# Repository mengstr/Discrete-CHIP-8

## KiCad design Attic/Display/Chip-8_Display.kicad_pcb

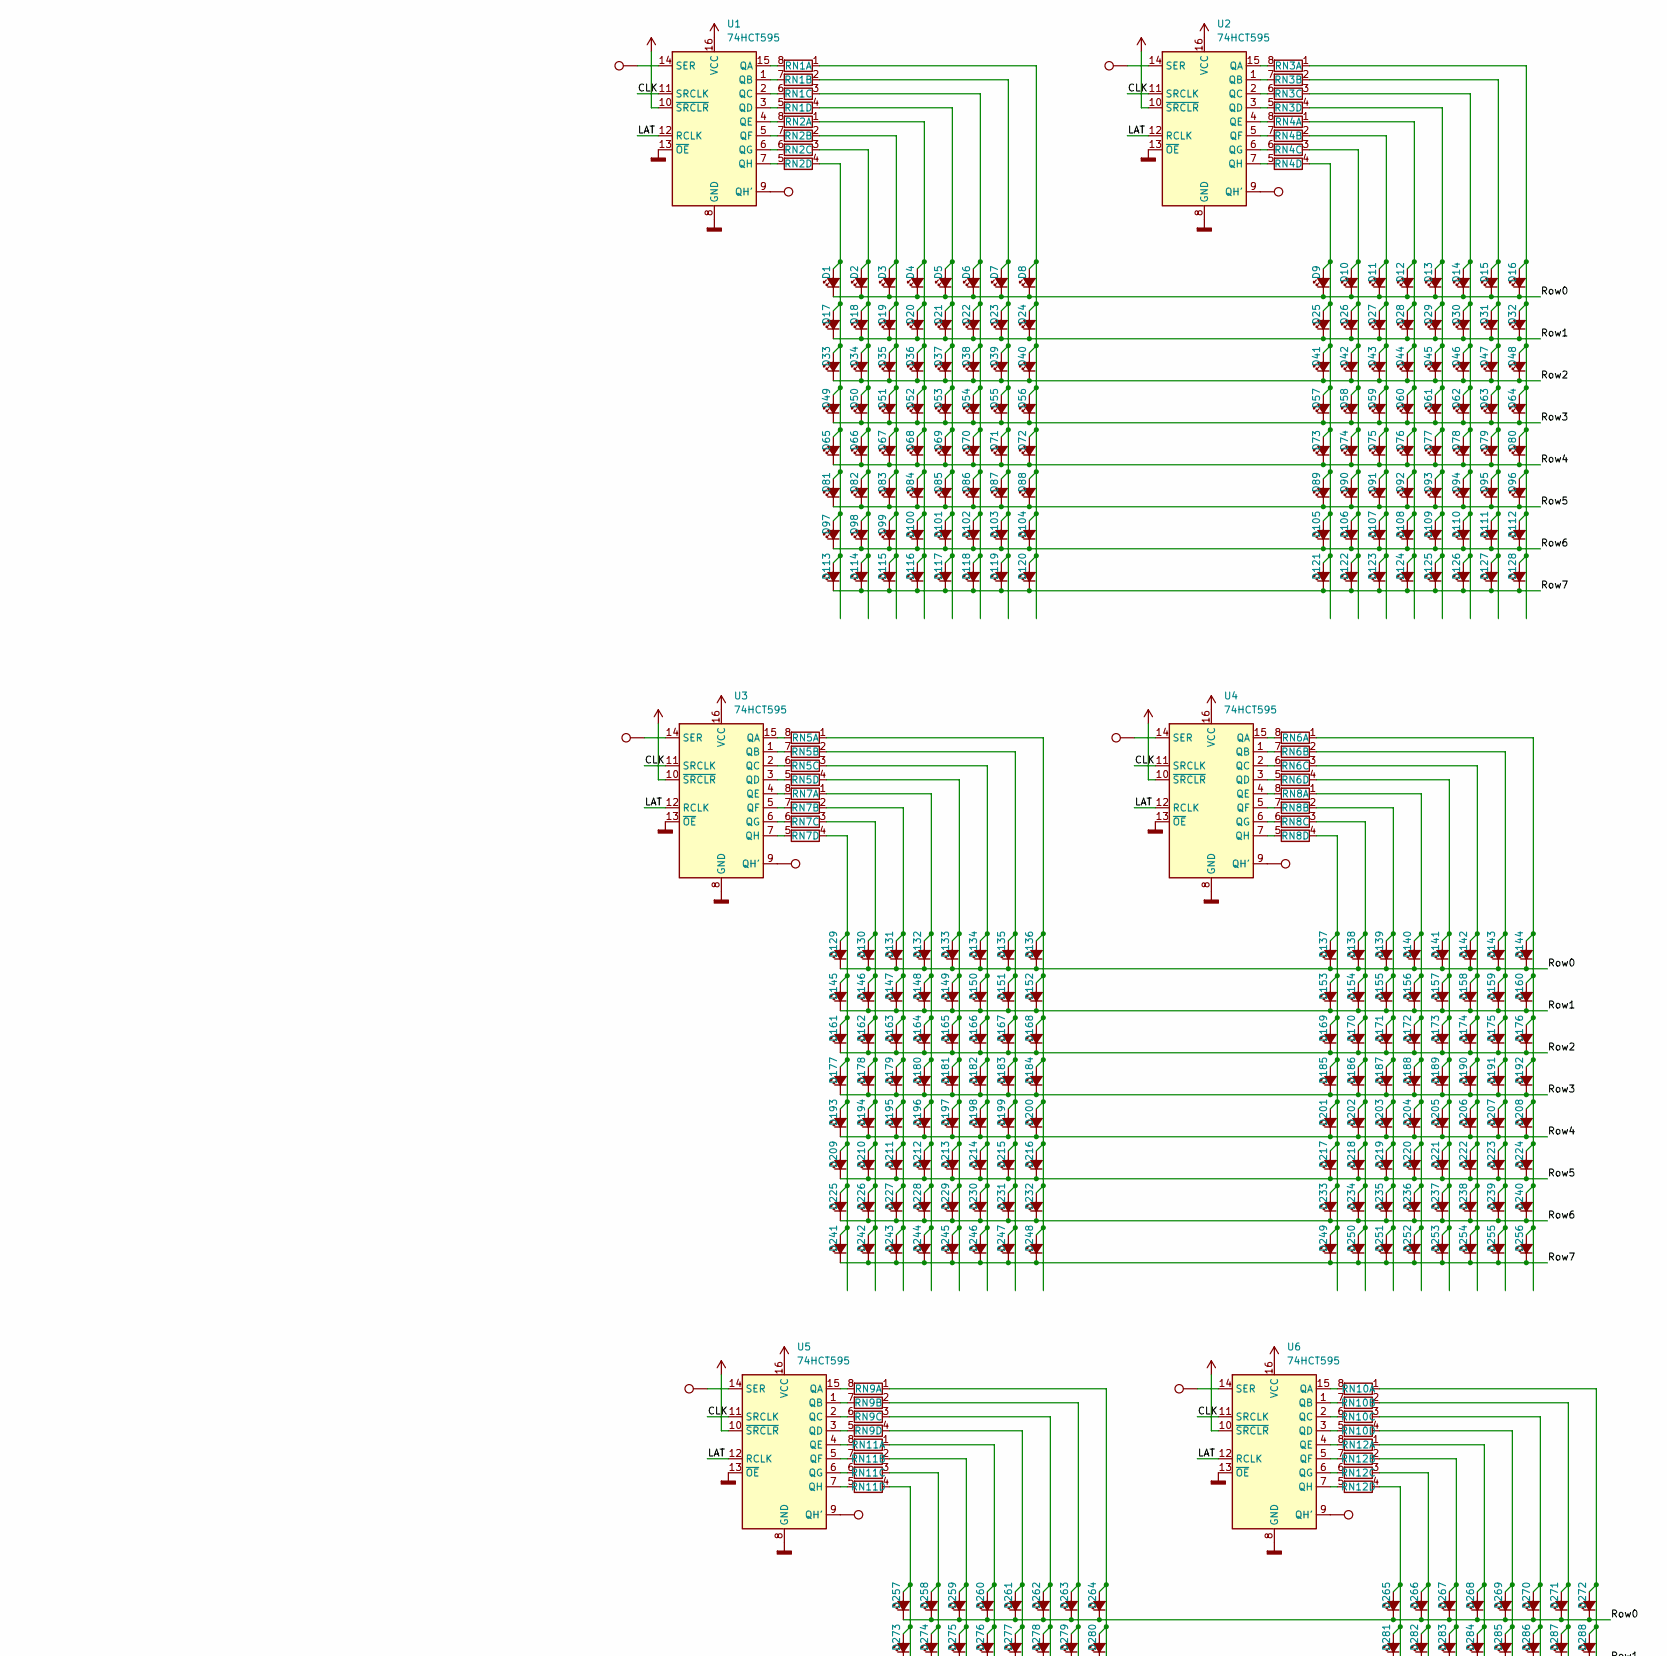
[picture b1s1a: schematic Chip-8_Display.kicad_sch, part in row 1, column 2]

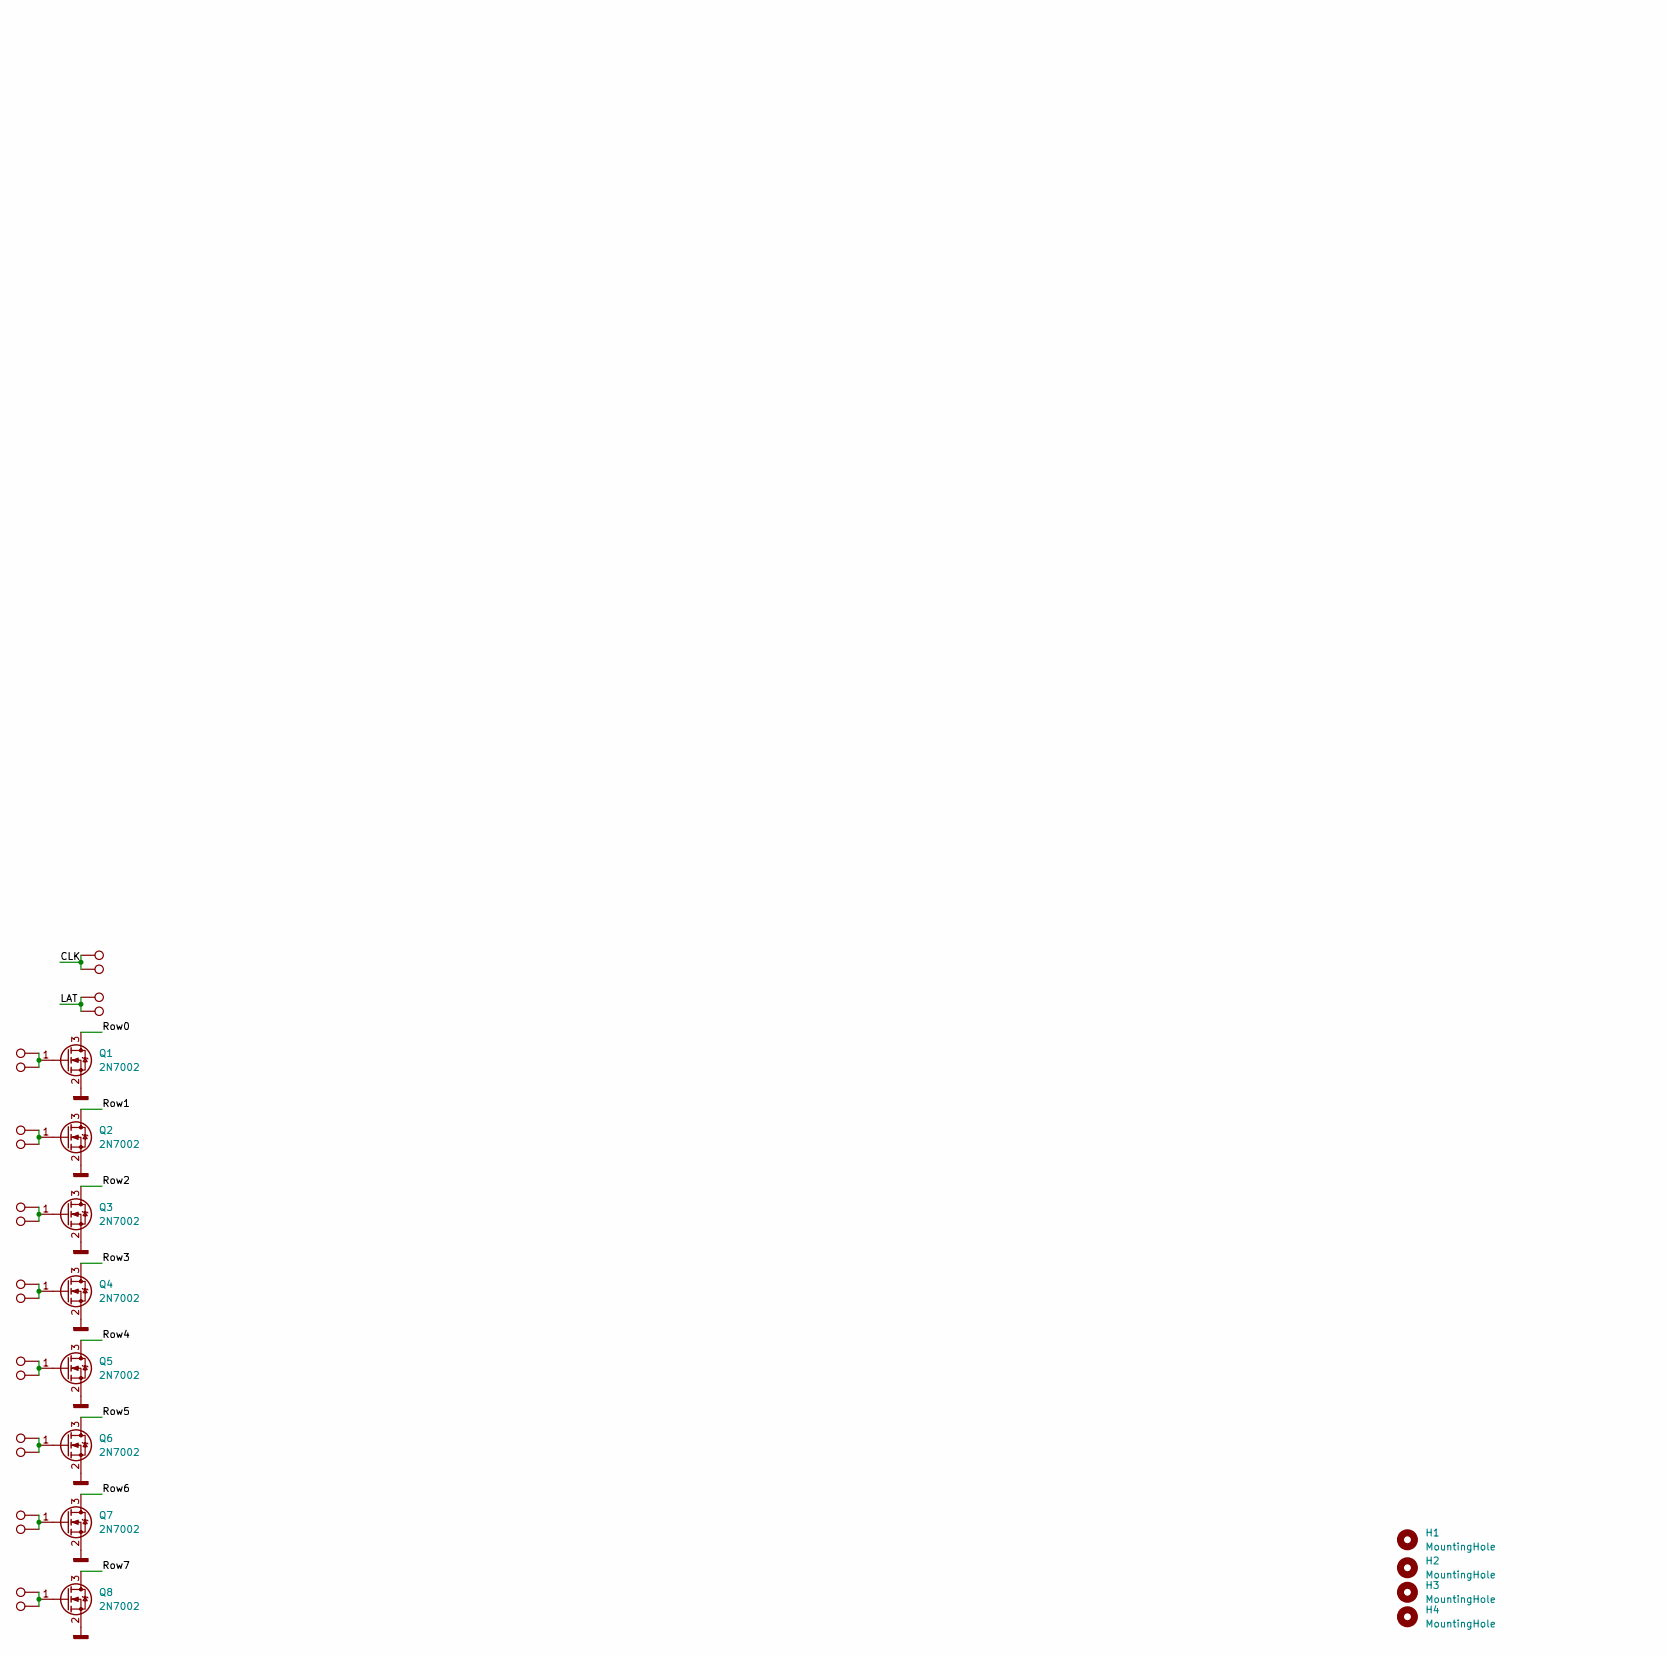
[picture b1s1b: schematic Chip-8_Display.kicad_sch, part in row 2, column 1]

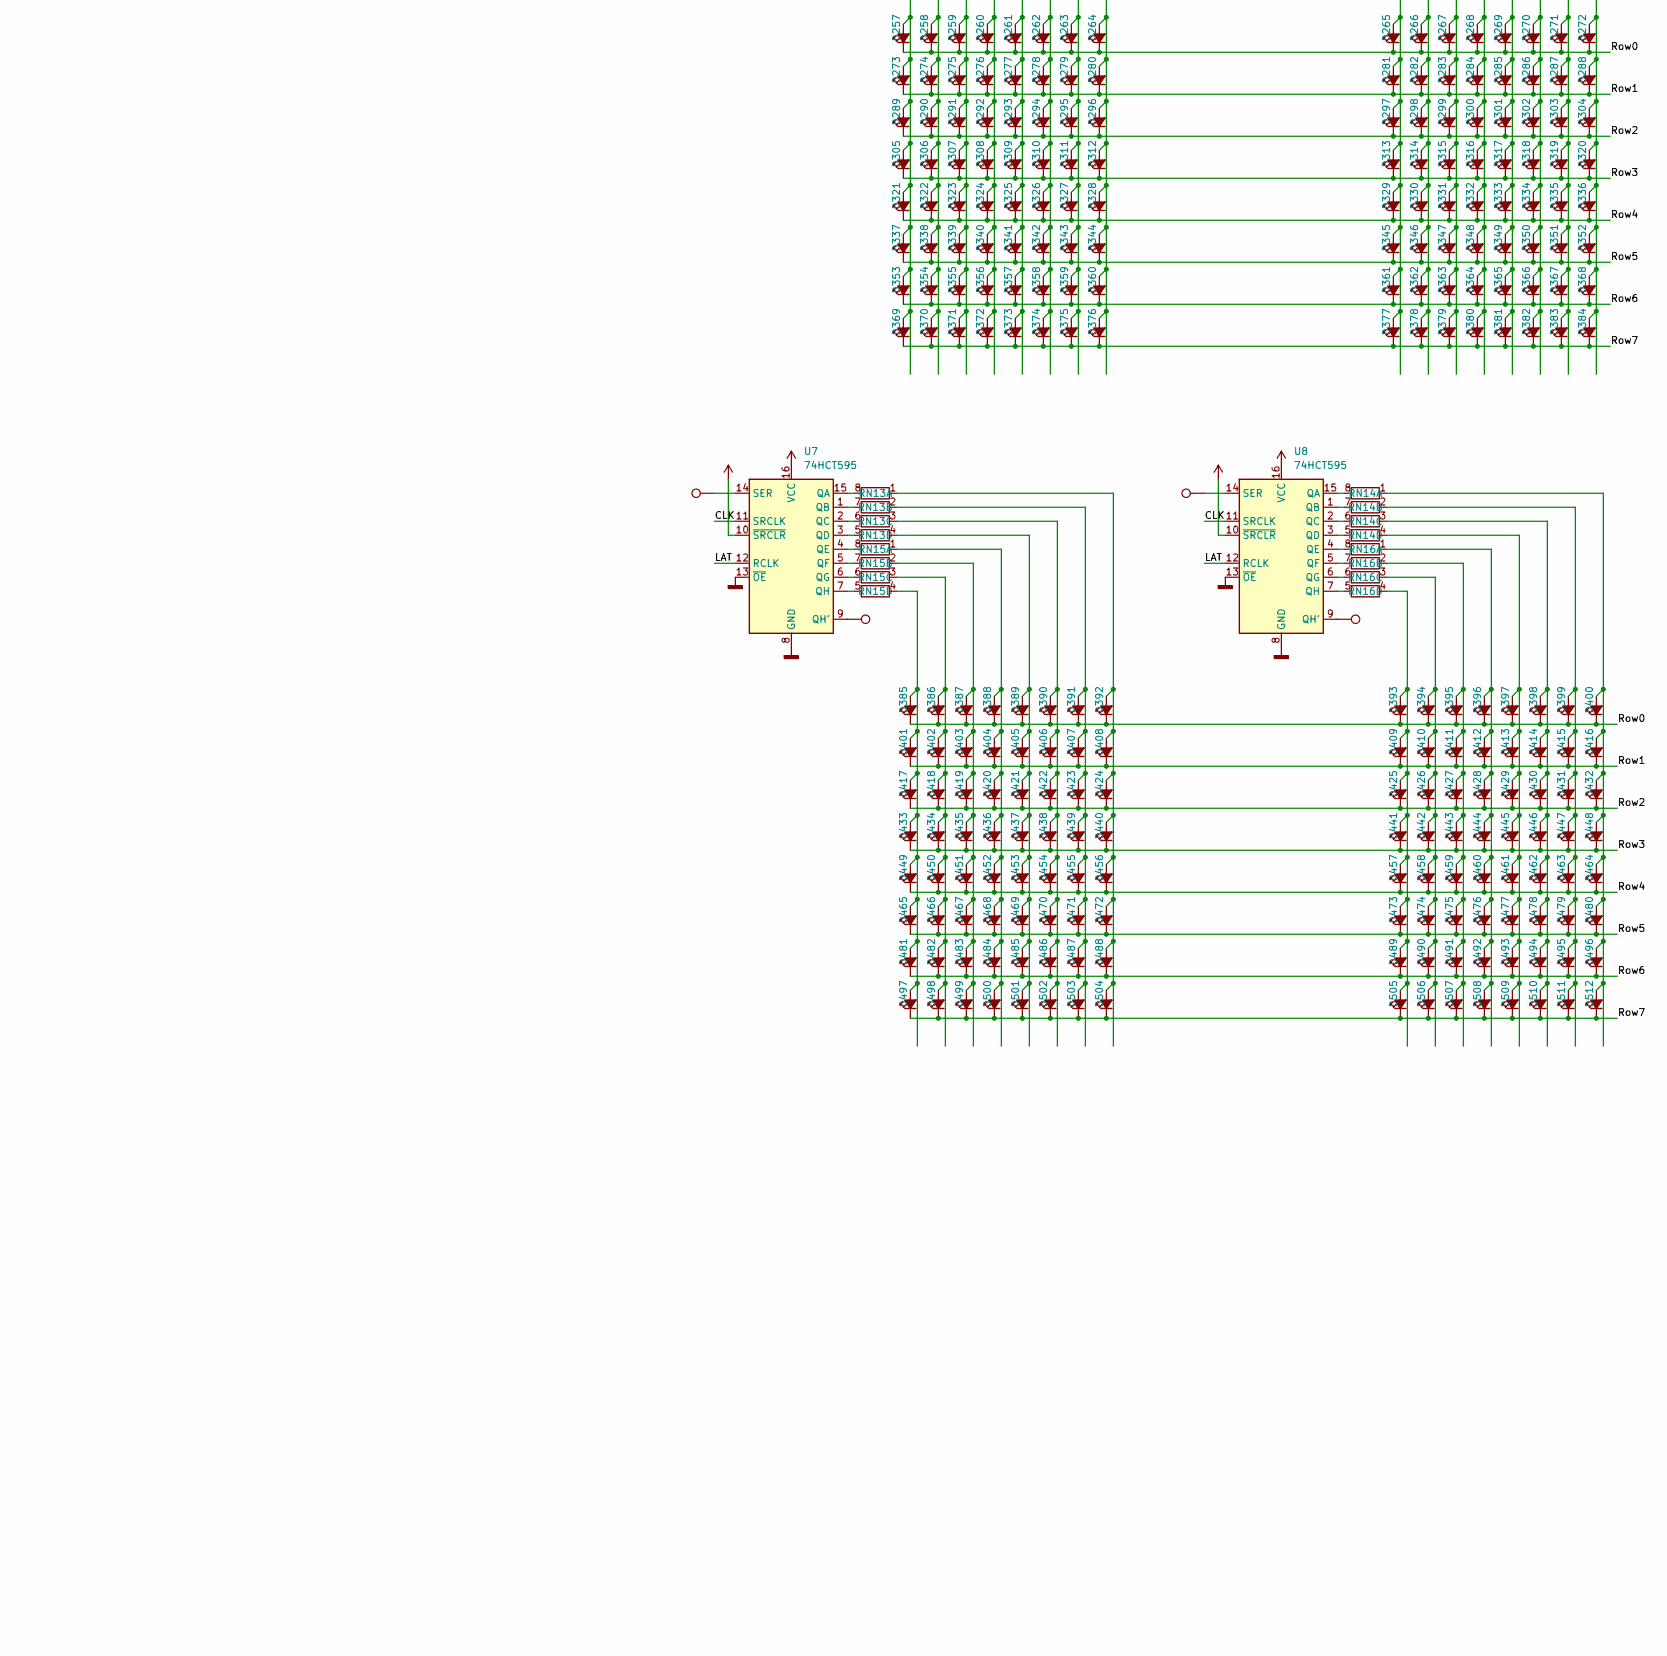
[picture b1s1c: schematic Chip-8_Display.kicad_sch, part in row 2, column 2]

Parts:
D1, D2, D3, D4, D5, D6, D7, D8, D9, D10, D11, D12, D13, D14, D15, D16, D17, D18, D19, D20, D21, D22, D23, D24, D25, D26, D27, D28, D29, D30, D31, D32, D33, D34, D35, D36, D37, D38, D39, D40, D41, D42, D43, D44, D45, D46, D47, D48, D49, D50, D51, D52, D53, D54, D55, D56, D57, D58, D59, D60, D61, D62, D63, D64, D65, D66, D67, D68, D69, D70, D71, D72, D73, D74, D75, D76, D77, D78, D79, D80, D81, D82, D83, D84, D85, D86, D87, D88, D89, D90, D91, D92, D93, D94, D95, D96, D97, D98, D99, D100, D101, D102, D103, D104, D105, D106, D107, D108, D109, D110, D111, D112, D113, D114, D115, D116, D117, D118, D119, D120, D121, D122, D123, D124, D125, D126, D127, D128, D129, D130, D131, D132, D133, D134, D135, D136, D137, D138, D139, D140, D141, D142, D143, D144, D145, D146, D147, D148, D149, D150, D151, D152, D153, D154, D155, D156, D157, D158, D159, D160, D161, D162, D163, D164, D165, D166, D167, D168, D169, D170, D171, D172, D173, D174, D175, D176, D177, D178, D179, D180, D181, D182, D183, D184, D185, D186, D187, D188, D189, D190, D191, D192, D193, D194, D195, D196, D197, D198, D199, D200, D201, D202, D203, D204, D205, D206, D207, D208, D209, D210, D211, D212, D213, D214, D215, D216, D217, D218, D219, D220, D221, D222, D223, D224, D225, D226, D227, D228, D229, D230, D231, D232, D233, D234, D235, D236, D237, D238, D239, D240, D241, D242, D243, D244, D245, D246, D247, D248, D249, D250, D251, D252, D253, D254, D255, D256, D257, D258, D259, D260, D261, D262, D263, D264, D265, D266, D267, D268, D269, D270, D271, D272, D273, D274, D275, D276, D277, D278, D279, D280, D281, D282, D283, D284, D285, D286, D287, D288, D289, D290, D291, D292, D293, D294, D295, D296, D297, D298, D299, D300, D301, D302, D303, D304, D305, D306, D307, D308, D309, D310, D311, D312, D313, D314, D315, D316, D317, D318, D319, D320, D321, D322, D323, D324, D325, D326, D327, D328, D329, D330, D331, D332, D333, D334, D335, D336, D337, D338, D339, D340, D341, D342, D343, D344, D345, D346, D347, D348, D349, D350, D351, D352, D353, D354, D355, D356, D357, D358, D359, D360, D361, D362, D363, D364, D365, D366, D367, D368, D369, D370, D371, D372, D373, D374, D375, D376, D377, D378, D379, D380, D381, D382, D383, D384, D385, D386, D387, D388, D389, D390, D391, D392, D393, D394, D395, D396, D397, D398, D399, D400, D401, D402, D403, D404, D405, D406, D407, D408, D409, D410, D411, D412, D413, D414, D415, D416, D417, D418, D419, D420, D421, D422, D423, D424, D425, D426, D427, D428, D429, D430, D431, D432, D433, D434, D435, D436, D437, D438, D439, D440, D441, D442, D443, D444, D445, D446, D447, D448, D449, D450, D451, D452, D453, D454, D455, D456, D457, D458, D459, D460, D461, D462, D463, D464, D465, D466, D467, D468, D469, D470, D471, D472, D473, D474, D475, D476, D477, D478, D479, D480, D481, D482, D483, D484, D485, D486, D487, D488, D489, D490, D491, D492, D493, D494, D495, D496, D497, D498, D499, D500, D501, D502, D503, D504, D505, D506, D507, D508, D509, D510, D511, D512: LED_Small_Filled; LED_0603_1608Metric
H1, H2, H3, H4: MountingHole; MountingHole_M2
Q1, Q2, Q3, Q4, Q5, Q6, Q7, Q8: 2N7002; SOT-23
RN1, RN2, RN3, RN4, RN5, RN6, RN7, RN8, RN9, RN10, RN11, RN12, RN13, RN14, RN15, RN16: R_Pack04_Split; R_Array_Concave_4x0603
TP1, TP2, TP3, TP4, TP5, TP6, TP7, TP8, TP9, TP10, TP11, TP12, TP13, TP14, TP15, TP16, TP17, TP18, TP19, TP20, TP21, TP22, TP23, TP24, TP25, TP26, TP27, TP28, TP29, TP30, TP31, TP32, TP33, TP34, TP35, TP36: TestPoint; TestPoint_Pad_D2.0mm
U1, U2, U3, U4, U5, U6, U7, U8: 74HCT595; SOIC-16_3.9x9.9mm_P1.27mm

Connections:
/CLK: TP25.1, TP26.1, U1.11 (SRCLK), U2.11 (SRCLK), U3.11 (SRCLK), U4.11 (SRCLK), U5.11 (SRCLK), U6.11 (SRCLK), U7.11 (SRCLK), U8.11 (SRCLK)
/LAT: TP27.1, TP28.1, U1.12 (RCLK), U2.12 (RCLK), U3.12 (RCLK), U4.12 (RCLK), U5.12 (RCLK), U6.12 (RCLK), U7.12 (RCLK), U8.12 (RCLK)
/Row0: D1.1 (K), D2.1 (K), D3.1 (K), D4.1 (K), D5.1 (K), D6.1 (K), D7.1 (K), D8.1 (K), D9.1 (K), D10.1 (K), D11.1 (K), D12.1 (K), D13.1 (K), D14.1 (K), D15.1 (K), D16.1 (K), D129.1 (K), D130.1 (K), D131.1 (K), D132.1 (K), D133.1 (K), D134.1 (K), D135.1 (K), D136.1 (K), D137.1 (K), D138.1 (K), D139.1 (K), D140.1 (K), D141.1 (K), D142.1 (K), D143.1 (K), D144.1 (K), D257.1 (K), D258.1 (K), D259.1 (K), D260.1 (K), D261.1 (K), D262.1 (K), D263.1 (K), D264.1 (K), D265.1 (K), D266.1 (K), D267.1 (K), D268.1 (K), D269.1 (K), D270.1 (K), D271.1 (K), D272.1 (K), D385.1 (K), D386.1 (K), D387.1 (K), D388.1 (K), D389.1 (K), D390.1 (K), D391.1 (K), D392.1 (K), D393.1 (K), D394.1 (K), D395.1 (K), D396.1 (K), D397.1 (K), D398.1 (K), D399.1 (K), D400.1 (K), Q1.3 (D)
/Row1: D17.1 (K), D18.1 (K), D19.1 (K), D20.1 (K), D21.1 (K), D22.1 (K), D23.1 (K), D24.1 (K), D25.1 (K), D26.1 (K), D27.1 (K), D28.1 (K), D29.1 (K), D30.1 (K), D31.1 (K), D32.1 (K), D145.1 (K), D146.1 (K), D147.1 (K), D148.1 (K), D149.1 (K), D150.1 (K), D151.1 (K), D152.1 (K), D153.1 (K), D154.1 (K), D155.1 (K), D156.1 (K), D157.1 (K), D158.1 (K), D159.1 (K), D160.1 (K), D273.1 (K), D274.1 (K), D275.1 (K), D276.1 (K), D277.1 (K), D278.1 (K), D279.1 (K), D280.1 (K), D281.1 (K), D282.1 (K), D283.1 (K), D284.1 (K), D285.1 (K), D286.1 (K), D287.1 (K), D288.1 (K), D401.1 (K), D402.1 (K), D403.1 (K), D404.1 (K), D405.1 (K), D406.1 (K), D407.1 (K), D408.1 (K), D409.1 (K), D410.1 (K), D411.1 (K), D412.1 (K), D413.1 (K), D414.1 (K), D415.1 (K), D416.1 (K), Q2.3 (D)
/Row2: D33.1 (K), D34.1 (K), D35.1 (K), D36.1 (K), D37.1 (K), D38.1 (K), D39.1 (K), D40.1 (K), D41.1 (K), D42.1 (K), D43.1 (K), D44.1 (K), D45.1 (K), D46.1 (K), D47.1 (K), D48.1 (K), D161.1 (K), D162.1 (K), D163.1 (K), D164.1 (K), D165.1 (K), D166.1 (K), D167.1 (K), D168.1 (K), D169.1 (K), D170.1 (K), D171.1 (K), D172.1 (K), D173.1 (K), D174.1 (K), D175.1 (K), D176.1 (K), D289.1 (K), D290.1 (K), D291.1 (K), D292.1 (K), D293.1 (K), D294.1 (K), D295.1 (K), D296.1 (K), D297.1 (K), D298.1 (K), D299.1 (K), D300.1 (K), D301.1 (K), D302.1 (K), D303.1 (K), D304.1 (K), D417.1 (K), D418.1 (K), D419.1 (K), D420.1 (K), D421.1 (K), D422.1 (K), D423.1 (K), D424.1 (K), D425.1 (K), D426.1 (K), D427.1 (K), D428.1 (K), D429.1 (K), D430.1 (K), D431.1 (K), D432.1 (K), Q3.3 (D)
/Row3: D49.1 (K), D50.1 (K), D51.1 (K), D52.1 (K), D53.1 (K), D54.1 (K), D55.1 (K), D56.1 (K), D57.1 (K), D58.1 (K), D59.1 (K), D60.1 (K), D61.1 (K), D62.1 (K), D63.1 (K), D64.1 (K), D177.1 (K), D178.1 (K), D179.1 (K), D180.1 (K), D181.1 (K), D182.1 (K), D183.1 (K), D184.1 (K), D185.1 (K), D186.1 (K), D187.1 (K), D188.1 (K), D189.1 (K), D190.1 (K), D191.1 (K), D192.1 (K), D305.1 (K), D306.1 (K), D307.1 (K), D308.1 (K), D309.1 (K), D310.1 (K), D311.1 (K), D312.1 (K), D313.1 (K), D314.1 (K), D315.1 (K), D316.1 (K), D317.1 (K), D318.1 (K), D319.1 (K), D320.1 (K), D433.1 (K), D434.1 (K), D435.1 (K), D436.1 (K), D437.1 (K), D438.1 (K), D439.1 (K), D440.1 (K), D441.1 (K), D442.1 (K), D443.1 (K), D444.1 (K), D445.1 (K), D446.1 (K), D447.1 (K), D448.1 (K), Q4.3 (D)
/Row4: D65.1 (K), D66.1 (K), D67.1 (K), D68.1 (K), D69.1 (K), D70.1 (K), D71.1 (K), D72.1 (K), D73.1 (K), D74.1 (K), D75.1 (K), D76.1 (K), D77.1 (K), D78.1 (K), D79.1 (K), D80.1 (K), D193.1 (K), D194.1 (K), D195.1 (K), D196.1 (K), D197.1 (K), D198.1 (K), D199.1 (K), D200.1 (K), D201.1 (K), D202.1 (K), D203.1 (K), D204.1 (K), D205.1 (K), D206.1 (K), D207.1 (K), D208.1 (K), D321.1 (K), D322.1 (K), D323.1 (K), D324.1 (K), D325.1 (K), D326.1 (K), D327.1 (K), D328.1 (K), D329.1 (K), D330.1 (K), D331.1 (K), D332.1 (K), D333.1 (K), D334.1 (K), D335.1 (K), D336.1 (K), D449.1 (K), D450.1 (K), D451.1 (K), D452.1 (K), D453.1 (K), D454.1 (K), D455.1 (K), D456.1 (K), D457.1 (K), D458.1 (K), D459.1 (K), D460.1 (K), D461.1 (K), D462.1 (K), D463.1 (K), D464.1 (K), Q5.3 (D)
/Row5: D81.1 (K), D82.1 (K), D83.1 (K), D84.1 (K), D85.1 (K), D86.1 (K), D87.1 (K), D88.1 (K), D89.1 (K), D90.1 (K), D91.1 (K), D92.1 (K), D93.1 (K), D94.1 (K), D95.1 (K), D96.1 (K), D209.1 (K), D210.1 (K), D211.1 (K), D212.1 (K), D213.1 (K), D214.1 (K), D215.1 (K), D216.1 (K), D217.1 (K), D218.1 (K), D219.1 (K), D220.1 (K), D221.1 (K), D222.1 (K), D223.1 (K), D224.1 (K), D337.1 (K), D338.1 (K), D339.1 (K), D340.1 (K), D341.1 (K), D342.1 (K), D343.1 (K), D344.1 (K), D345.1 (K), D346.1 (K), D347.1 (K), D348.1 (K), D349.1 (K), D350.1 (K), D351.1 (K), D352.1 (K), D465.1 (K), D466.1 (K), D467.1 (K), D468.1 (K), D469.1 (K), D470.1 (K), D471.1 (K), D472.1 (K), D473.1 (K), D474.1 (K), D475.1 (K), D476.1 (K), D477.1 (K), D478.1 (K), D479.1 (K), D480.1 (K), Q6.3 (D)
/Row6: D97.1 (K), D98.1 (K), D99.1 (K), D100.1 (K), D101.1 (K), D102.1 (K), D103.1 (K), D104.1 (K), D105.1 (K), D106.1 (K), D107.1 (K), D108.1 (K), D109.1 (K), D110.1 (K), D111.1 (K), D112.1 (K), D225.1 (K), D226.1 (K), D227.1 (K), D228.1 (K), D229.1 (K), D230.1 (K), D231.1 (K), D232.1 (K), D233.1 (K), D234.1 (K), D235.1 (K), D236.1 (K), D237.1 (K), D238.1 (K), D239.1 (K), D240.1 (K), D353.1 (K), D354.1 (K), D355.1 (K), D356.1 (K), D357.1 (K), D358.1 (K), D359.1 (K), D360.1 (K), D361.1 (K), D362.1 (K), D363.1 (K), D364.1 (K), D365.1 (K), D366.1 (K), D367.1 (K), D368.1 (K), D481.1 (K), D482.1 (K), D483.1 (K), D484.1 (K), D485.1 (K), D486.1 (K), D487.1 (K), D488.1 (K), D489.1 (K), D490.1 (K), D491.1 (K), D492.1 (K), D493.1 (K), D494.1 (K), D495.1 (K), D496.1 (K), Q7.3 (D)
/Row7: D113.1 (K), D114.1 (K), D115.1 (K), D116.1 (K), D117.1 (K), D118.1 (K), D119.1 (K), D120.1 (K), D121.1 (K), D122.1 (K), D123.1 (K), D124.1 (K), D125.1 (K), D126.1 (K), D127.1 (K), D128.1 (K), D241.1 (K), D242.1 (K), D243.1 (K), D244.1 (K), D245.1 (K), D246.1 (K), D247.1 (K), D248.1 (K), D249.1 (K), D250.1 (K), D251.1 (K), D252.1 (K), D253.1 (K), D254.1 (K), D255.1 (K), D256.1 (K), D369.1 (K), D370.1 (K), D371.1 (K), D372.1 (K), D373.1 (K), D374.1 (K), D375.1 (K), D376.1 (K), D377.1 (K), D378.1 (K), D379.1 (K), D380.1 (K), D381.1 (K), D382.1 (K), D383.1 (K), D384.1 (K), D497.1 (K), D498.1 (K), D499.1 (K), D500.1 (K), D501.1 (K), D502.1 (K), D503.1 (K), D504.1 (K), D505.1 (K), D506.1 (K), D507.1 (K), D508.1 (K), D509.1 (K), D510.1 (K), D511.1 (K), D512.1 (K), Q8.3 (D)
GNDD: Q1.2 (S), Q2.2 (S), Q3.2 (S), Q4.2 (S), Q5.2 (S), Q6.2 (S), Q7.2 (S), Q8.2 (S), U1.8 (GND), U1.13 (~OE), U2.8 (GND), U2.13 (~OE), U3.8 (GND), U3.13 (~OE), U4.8 (GND), U4.13 (~OE), U5.8 (GND), U5.13 (~OE), U6.8 (GND), U6.13 (~OE), U7.8 (GND), U7.13 (~OE), U8.8 (GND), U8.13 (~OE)
unnamed: D1.2 (A), D17.2 (A), D33.2 (A), D49.2 (A), D65.2 (A), D81.2 (A), D97.2 (A), D113.2 (A), RN2.4 (R4.1)
unnamed: D10.2 (A), D26.2 (A), D42.2 (A), D58.2 (A), D74.2 (A), D90.2 (A), D106.2 (A), D122.2 (A), RN4.3 (R3.1)
unnamed: D4.2 (A), D20.2 (A), D36.2 (A), D52.2 (A), D68.2 (A), D84.2 (A), D100.2 (A), D116.2 (A), RN2.1 (R1.1)
unnamed: D5.2 (A), D21.2 (A), D37.2 (A), D53.2 (A), D69.2 (A), D85.2 (A), D101.2 (A), D117.2 (A), RN1.4 (R4.1)
unnamed: D6.2 (A), D22.2 (A), D38.2 (A), D54.2 (A), D70.2 (A), D86.2 (A), D102.2 (A), D118.2 (A), RN1.3 (R3.1)
unnamed: D7.2 (A), D23.2 (A), D39.2 (A), D55.2 (A), D71.2 (A), D87.2 (A), D103.2 (A), D119.2 (A), RN1.2 (R2.1)
unnamed: D8.2 (A), D24.2 (A), D40.2 (A), D56.2 (A), D72.2 (A), D88.2 (A), D104.2 (A), D120.2 (A), RN1.1 (R1.1)
unnamed: D9.2 (A), D25.2 (A), D41.2 (A), D57.2 (A), D73.2 (A), D89.2 (A), D105.2 (A), D121.2 (A), RN4.4 (R4.1)
unnamed: D11.2 (A), D27.2 (A), D43.2 (A), D59.2 (A), D75.2 (A), D91.2 (A), D107.2 (A), D123.2 (A), RN4.2 (R2.1)
unnamed: D12.2 (A), D28.2 (A), D44.2 (A), D60.2 (A), D76.2 (A), D92.2 (A), D108.2 (A), D124.2 (A), RN4.1 (R1.1)
unnamed: D13.2 (A), D29.2 (A), D45.2 (A), D61.2 (A), D77.2 (A), D93.2 (A), D109.2 (A), D125.2 (A), RN3.4 (R4.1)
unnamed: D14.2 (A), D30.2 (A), D46.2 (A), D62.2 (A), D78.2 (A), D94.2 (A), D110.2 (A), D126.2 (A), RN3.3 (R3.1)
unnamed: D15.2 (A), D31.2 (A), D47.2 (A), D63.2 (A), D79.2 (A), D95.2 (A), D111.2 (A), D127.2 (A), RN3.2 (R2.1)
unnamed: D16.2 (A), D32.2 (A), D48.2 (A), D64.2 (A), D80.2 (A), D96.2 (A), D112.2 (A), D128.2 (A), RN3.1 (R1.1)
unnamed: D2.2 (A), D18.2 (A), D34.2 (A), D50.2 (A), D66.2 (A), D82.2 (A), D98.2 (A), D114.2 (A), RN2.3 (R3.1)
unnamed: D3.2 (A), D19.2 (A), D35.2 (A), D51.2 (A), D67.2 (A), D83.2 (A), D99.2 (A), D115.2 (A), RN2.2 (R2.1)
unnamed: D129.2 (A), D145.2 (A), D161.2 (A), D177.2 (A), D193.2 (A), D209.2 (A), D225.2 (A), D241.2 (A), RN7.4 (R4.1)
unnamed: D130.2 (A), D146.2 (A), D162.2 (A), D178.2 (A), D194.2 (A), D210.2 (A), D226.2 (A), D242.2 (A), RN7.3 (R3.1)
unnamed: D131.2 (A), D147.2 (A), D163.2 (A), D179.2 (A), D195.2 (A), D211.2 (A), D227.2 (A), D243.2 (A), RN7.2 (R2.1)
unnamed: D132.2 (A), D148.2 (A), D164.2 (A), D180.2 (A), D196.2 (A), D212.2 (A), D228.2 (A), D244.2 (A), RN7.1 (R1.1)
unnamed: D133.2 (A), D149.2 (A), D165.2 (A), D181.2 (A), D197.2 (A), D213.2 (A), D229.2 (A), D245.2 (A), RN5.4 (R4.1)
unnamed: D134.2 (A), D150.2 (A), D166.2 (A), D182.2 (A), D198.2 (A), D214.2 (A), D230.2 (A), D246.2 (A), RN5.3 (R3.1)
unnamed: D135.2 (A), D151.2 (A), D167.2 (A), D183.2 (A), D199.2 (A), D215.2 (A), D231.2 (A), D247.2 (A), RN5.2 (R2.1)
unnamed: D136.2 (A), D152.2 (A), D168.2 (A), D184.2 (A), D200.2 (A), D216.2 (A), D232.2 (A), D248.2 (A), RN5.1 (R1.1)
unnamed: D137.2 (A), D153.2 (A), D169.2 (A), D185.2 (A), D201.2 (A), D217.2 (A), D233.2 (A), D249.2 (A), RN8.4 (R4.1)
unnamed: D138.2 (A), D154.2 (A), D170.2 (A), D186.2 (A), D202.2 (A), D218.2 (A), D234.2 (A), D250.2 (A), RN8.3 (R3.1)
unnamed: D139.2 (A), D155.2 (A), D171.2 (A), D187.2 (A), D203.2 (A), D219.2 (A), D235.2 (A), D251.2 (A), RN8.2 (R2.1)
unnamed: D140.2 (A), D156.2 (A), D172.2 (A), D188.2 (A), D204.2 (A), D220.2 (A), D236.2 (A), D252.2 (A), RN8.1 (R1.1)
unnamed: D141.2 (A), D157.2 (A), D173.2 (A), D189.2 (A), D205.2 (A), D221.2 (A), D237.2 (A), D253.2 (A), RN6.4 (R4.1)
unnamed: D142.2 (A), D158.2 (A), D174.2 (A), D190.2 (A), D206.2 (A), D222.2 (A), D238.2 (A), D254.2 (A), RN6.3 (R3.1)
unnamed: D143.2 (A), D159.2 (A), D175.2 (A), D191.2 (A), D207.2 (A), D223.2 (A), D239.2 (A), D255.2 (A), RN6.2 (R2.1)
unnamed: D144.2 (A), D160.2 (A), D176.2 (A), D192.2 (A), D208.2 (A), D224.2 (A), D240.2 (A), D256.2 (A), RN6.1 (R1.1)
unnamed: D257.2 (A), D273.2 (A), D289.2 (A), D305.2 (A), D321.2 (A), D337.2 (A), D353.2 (A), D369.2 (A), RN11.4 (R4.1)
unnamed: D258.2 (A), D274.2 (A), D290.2 (A), D306.2 (A), D322.2 (A), D338.2 (A), D354.2 (A), D370.2 (A), RN11.3 (R3.1)
unnamed: D259.2 (A), D275.2 (A), D291.2 (A), D307.2 (A), D323.2 (A), D339.2 (A), D355.2 (A), D371.2 (A), RN11.2 (R2.1)
unnamed: D260.2 (A), D276.2 (A), D292.2 (A), D308.2 (A), D324.2 (A), D340.2 (A), D356.2 (A), D372.2 (A), RN11.1 (R1.1)
unnamed: D261.2 (A), D277.2 (A), D293.2 (A), D309.2 (A), D325.2 (A), D341.2 (A), D357.2 (A), D373.2 (A), RN9.4 (R4.1)
unnamed: D262.2 (A), D278.2 (A), D294.2 (A), D310.2 (A), D326.2 (A), D342.2 (A), D358.2 (A), D374.2 (A), RN9.3 (R3.1)
unnamed: D263.2 (A), D279.2 (A), D295.2 (A), D311.2 (A), D327.2 (A), D343.2 (A), D359.2 (A), D375.2 (A), RN9.2 (R2.1)
unnamed: D264.2 (A), D280.2 (A), D296.2 (A), D312.2 (A), D328.2 (A), D344.2 (A), D360.2 (A), D376.2 (A), RN9.1 (R1.1)
unnamed: D265.2 (A), D281.2 (A), D297.2 (A), D313.2 (A), D329.2 (A), D345.2 (A), D361.2 (A), D377.2 (A), RN12.4 (R4.1)
unnamed: D266.2 (A), D282.2 (A), D298.2 (A), D314.2 (A), D330.2 (A), D346.2 (A), D362.2 (A), D378.2 (A), RN12.3 (R3.1)
unnamed: D267.2 (A), D283.2 (A), D299.2 (A), D315.2 (A), D331.2 (A), D347.2 (A), D363.2 (A), D379.2 (A), RN12.2 (R2.1)
unnamed: D268.2 (A), D284.2 (A), D300.2 (A), D316.2 (A), D332.2 (A), D348.2 (A), D364.2 (A), D380.2 (A), RN12.1 (R1.1)
unnamed: D269.2 (A), D285.2 (A), D301.2 (A), D317.2 (A), D333.2 (A), D349.2 (A), D365.2 (A), D381.2 (A), RN10.4 (R4.1)
unnamed: D270.2 (A), D286.2 (A), D302.2 (A), D318.2 (A), D334.2 (A), D350.2 (A), D366.2 (A), D382.2 (A), RN10.3 (R3.1)
unnamed: D271.2 (A), D287.2 (A), D303.2 (A), D319.2 (A), D335.2 (A), D351.2 (A), D367.2 (A), D383.2 (A), RN10.2 (R2.1)
unnamed: D272.2 (A), D288.2 (A), D304.2 (A), D320.2 (A), D336.2 (A), D352.2 (A), D368.2 (A), D384.2 (A), RN10.1 (R1.1)
unnamed: D385.2 (A), D401.2 (A), D417.2 (A), D433.2 (A), D449.2 (A), D465.2 (A), D481.2 (A), D497.2 (A), RN15.4 (R4.1)
unnamed: D386.2 (A), D402.2 (A), D418.2 (A), D434.2 (A), D450.2 (A), D466.2 (A), D482.2 (A), D498.2 (A), RN15.3 (R3.1)
unnamed: D387.2 (A), D403.2 (A), D419.2 (A), D435.2 (A), D451.2 (A), D467.2 (A), D483.2 (A), D499.2 (A), RN15.2 (R2.1)
unnamed: D388.2 (A), D404.2 (A), D420.2 (A), D436.2 (A), D452.2 (A), D468.2 (A), D484.2 (A), D500.2 (A), RN15.1 (R1.1)
unnamed: D389.2 (A), D405.2 (A), D421.2 (A), D437.2 (A), D453.2 (A), D469.2 (A), D485.2 (A), D501.2 (A), RN13.4 (R4.1)
unnamed: D390.2 (A), D406.2 (A), D422.2 (A), D438.2 (A), D454.2 (A), D470.2 (A), D486.2 (A), D502.2 (A), RN13.3 (R3.1)
unnamed: D391.2 (A), D407.2 (A), D423.2 (A), D439.2 (A), D455.2 (A), D471.2 (A), D487.2 (A), D503.2 (A), RN13.2 (R2.1)
unnamed: D392.2 (A), D408.2 (A), D424.2 (A), D440.2 (A), D456.2 (A), D472.2 (A), D488.2 (A), D504.2 (A), RN13.1 (R1.1)
unnamed: D393.2 (A), D409.2 (A), D425.2 (A), D441.2 (A), D457.2 (A), D473.2 (A), D489.2 (A), D505.2 (A), RN16.4 (R4.1)
unnamed: D394.2 (A), D410.2 (A), D426.2 (A), D442.2 (A), D458.2 (A), D474.2 (A), D490.2 (A), D506.2 (A), RN16.3 (R3.1)
unnamed: D395.2 (A), D411.2 (A), D427.2 (A), D443.2 (A), D459.2 (A), D475.2 (A), D491.2 (A), D507.2 (A), RN16.2 (R2.1)
unnamed: D396.2 (A), D412.2 (A), D428.2 (A), D444.2 (A), D460.2 (A), D476.2 (A), D492.2 (A), D508.2 (A), RN16.1 (R1.1)
unnamed: D397.2 (A), D413.2 (A), D429.2 (A), D445.2 (A), D461.2 (A), D477.2 (A), D493.2 (A), D509.2 (A), RN14.4 (R4.1)
unnamed: D398.2 (A), D414.2 (A), D430.2 (A), D446.2 (A), D462.2 (A), D478.2 (A), D494.2 (A), D510.2 (A), RN14.3 (R3.1)
unnamed: D399.2 (A), D415.2 (A), D431.2 (A), D447.2 (A), D463.2 (A), D479.2 (A), D495.2 (A), D511.2 (A), RN14.2 (R2.1)
unnamed: D400.2 (A), D416.2 (A), D432.2 (A), D448.2 (A), D464.2 (A), D480.2 (A), D496.2 (A), D512.2 (A), RN14.1 (R1.1)
unnamed: Q1.1 (G), TP1.1, TP2.1
unnamed: Q2.1 (G), TP3.1, TP4.1
unnamed: Q3.1 (G), TP5.1, TP6.1
unnamed: Q4.1 (G), TP7.1, TP8.1
unnamed: Q5.1 (G), TP9.1, TP10.1
unnamed: Q6.1 (G), TP11.1, TP12.1
unnamed: Q7.1 (G), TP13.1, TP14.1
unnamed: Q8.1 (G), TP15.1, TP16.1
unnamed: RN1.8 (R1.2), U1.15 (QA)
unnamed: RN1.7 (R2.2), U1.1 (QB)
unnamed: RN1.6 (R3.2), U1.2 (QC)
unnamed: RN1.5 (R4.2), U1.3 (QD)
unnamed: RN2.8 (R1.2), U1.4 (QE)
unnamed: RN2.7 (R2.2), U1.5 (QF)
unnamed: RN2.6 (R3.2), U1.6 (QG)
unnamed: RN2.5 (R4.2), U1.7 (QH)
unnamed: RN3.8 (R1.2), U2.15 (QA)
unnamed: RN3.7 (R2.2), U2.1 (QB)
unnamed: RN3.6 (R3.2), U2.2 (QC)
unnamed: RN3.5 (R4.2), U2.3 (QD)
unnamed: RN4.8 (R1.2), U2.4 (QE)
unnamed: RN4.7 (R2.2), U2.5 (QF)
unnamed: RN4.6 (R3.2), U2.6 (QG)
unnamed: RN4.5 (R4.2), U2.7 (QH)
unnamed: RN5.8 (R1.2), U3.15 (QA)
unnamed: RN5.7 (R2.2), U3.1 (QB)
unnamed: RN5.6 (R3.2), U3.2 (QC)
unnamed: RN5.5 (R4.2), U3.3 (QD)
unnamed: RN6.8 (R1.2), U4.15 (QA)
unnamed: RN6.7 (R2.2), U4.1 (QB)
unnamed: RN6.6 (R3.2), U4.2 (QC)
unnamed: RN6.5 (R4.2), U4.3 (QD)
unnamed: RN7.8 (R1.2), U3.4 (QE)
unnamed: RN7.7 (R2.2), U3.5 (QF)
unnamed: RN7.6 (R3.2), U3.6 (QG)
unnamed: RN7.5 (R4.2), U3.7 (QH)
unnamed: RN8.8 (R1.2), U4.4 (QE)
unnamed: RN8.7 (R2.2), U4.5 (QF)
unnamed: RN8.6 (R3.2), U4.6 (QG)
unnamed: RN8.5 (R4.2), U4.7 (QH)
unnamed: RN9.8 (R1.2), U5.15 (QA)
unnamed: RN9.7 (R2.2), U5.1 (QB)
unnamed: RN9.6 (R3.2), U5.2 (QC)
unnamed: RN9.5 (R4.2), U5.3 (QD)
unnamed: RN10.8 (R1.2), U6.15 (QA)
unnamed: RN10.7 (R2.2), U6.1 (QB)
unnamed: RN10.6 (R3.2), U6.2 (QC)
unnamed: RN10.5 (R4.2), U6.3 (QD)
unnamed: RN11.8 (R1.2), U5.4 (QE)
unnamed: RN11.7 (R2.2), U5.5 (QF)
unnamed: RN11.6 (R3.2), U5.6 (QG)
unnamed: RN11.5 (R4.2), U5.7 (QH)
unnamed: RN12.8 (R1.2), U6.4 (QE)
unnamed: RN12.7 (R2.2), U6.5 (QF)
unnamed: RN12.6 (R3.2), U6.6 (QG)
unnamed: RN12.5 (R4.2), U6.7 (QH)
unnamed: RN13.8 (R1.2), U7.15 (QA)
unnamed: RN13.7 (R2.2), U7.1 (QB)
unnamed: RN13.6 (R3.2), U7.2 (QC)
unnamed: RN13.5 (R4.2), U7.3 (QD)
unnamed: RN14.8 (R1.2), U8.15 (QA)
unnamed: RN14.7 (R2.2), U8.1 (QB)
unnamed: RN14.6 (R3.2), U8.2 (QC)
unnamed: RN14.5 (R4.2), U8.3 (QD)
unnamed: RN15.8 (R1.2), U7.4 (QE)
unnamed: RN15.7 (R2.2), U7.5 (QF)
unnamed: RN15.6 (R3.2), U7.6 (QG)
unnamed: RN15.5 (R4.2), U7.7 (QH)
unnamed: RN16.8 (R1.2), U8.4 (QE)
unnamed: RN16.7 (R2.2), U8.5 (QF)
unnamed: RN16.6 (R3.2), U8.6 (QG)
unnamed: RN16.5 (R4.2), U8.7 (QH)
unnamed: TP18.1, U1.9 (QH')
unnamed: TP17.1, U1.14 (SER)
unnamed: TP20.1, U2.9 (QH')
unnamed: TP19.1, U2.14 (SER)
unnamed: TP23.1, U3.9 (QH')
unnamed: TP21.1, U3.14 (SER)
unnamed: TP24.1, U4.9 (QH')
unnamed: TP22.1, U4.14 (SER)
unnamed: TP31.1, U5.9 (QH')
unnamed: TP29.1, U5.14 (SER)
unnamed: TP32.1, U6.9 (QH')
unnamed: TP30.1, U6.14 (SER)
unnamed: TP35.1, U7.9 (QH')
unnamed: TP33.1, U7.14 (SER)
unnamed: TP36.1, U8.9 (QH')
unnamed: TP34.1, U8.14 (SER)
VCC: U1.10 (~SRCLR), U1.16 (VCC), U2.10 (~SRCLR), U2.16 (VCC), U3.10 (~SRCLR), U3.16 (VCC), U4.10 (~SRCLR), U4.16 (VCC), U5.10 (~SRCLR), U5.16 (VCC), U6.10 (~SRCLR), U6.16 (VCC), U7.10 (~SRCLR), U7.16 (VCC), U8.10 (~SRCLR), U8.16 (VCC)
